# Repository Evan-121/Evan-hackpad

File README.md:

# Evan-hackpad

i used an oled screen, 9 keys/switches, and a xiao prosessor 

all the switches anre linked into the xiao and so is the oled so when i plug it in i can program the buttons to run spesific functions

i will use it to game controll music and  use it to controll some of my other arduino/razberry pi progects

i then designed the case in fusion and brought in the pcb to test the fit

i then got the modells from grabcad and assembled it all in fusion

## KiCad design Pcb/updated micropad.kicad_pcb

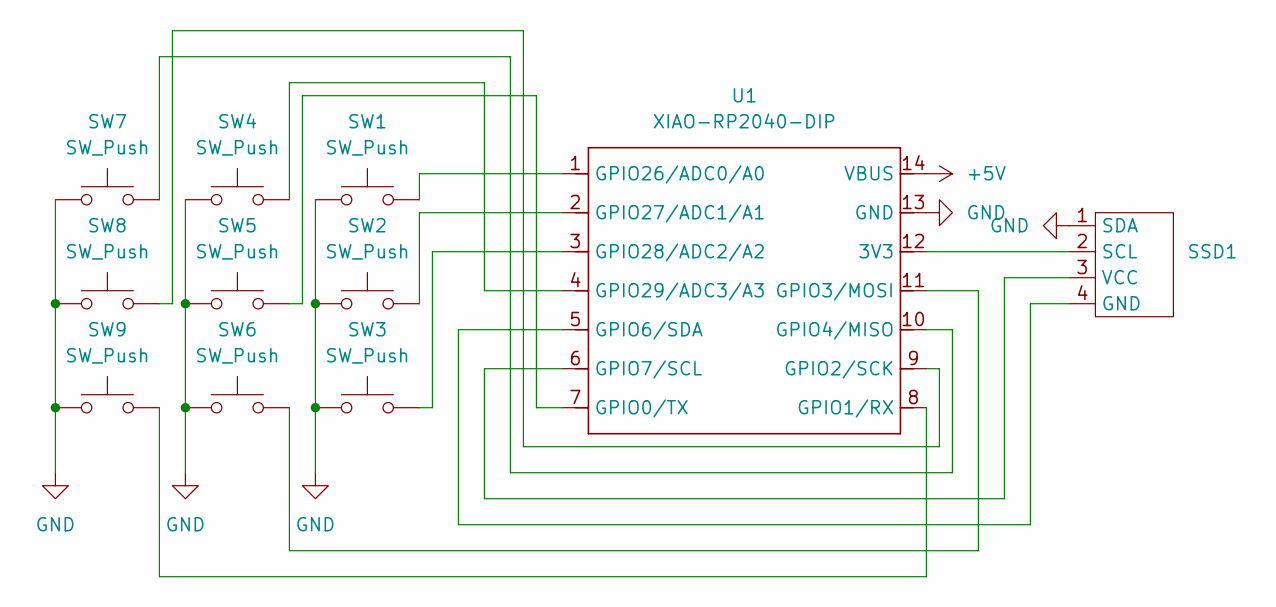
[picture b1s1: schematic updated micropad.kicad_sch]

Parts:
SSD1: SSD1306-0.91-OLED-4pin-128x32 (4)
SW1, SW2, SW3, SW4, SW5, SW6, SW7, SW8, SW9: SW_Push; SW_Cherry_MX_1.00u_PCB
U1: XIAO-RP2040-DIP

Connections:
+5V: U1.14 (VBUS)
GND: SSD1.1 (SDA), SW1.1, SW2.1, SW3.1, SW4.1, SW5.1, SW6.1, SW7.1, SW8.1, SW9.1, U1.13 (GND)
unnamed: SSD1.4 (GND), U1.5 (GPIO6/SDA)
unnamed: SSD1.2 (SCL), U1.12 (3V3)
unnamed: SSD1.3 (VCC), U1.6 (GPIO7/SCL)
unnamed: SW5.2, U1.7 (GPIO0/TX)
unnamed: SW9.2, U1.8 (GPIO1/RX)
unnamed: SW8.2, U1.9 (GPIO2/SCK)
unnamed: SW6.2, U1.11 (GPIO3/MOSI)
unnamed: SW7.2, U1.10 (GPIO4/MISO)
unnamed: SW1.2, U1.1 (GPIO26/ADC0/A0)
unnamed: SW2.2, U1.2 (GPIO27/ADC1/A1)
unnamed: SW3.2, U1.3 (GPIO28/ADC2/A2)
unnamed: SW4.2, U1.4 (GPIO29/ADC3/A3)

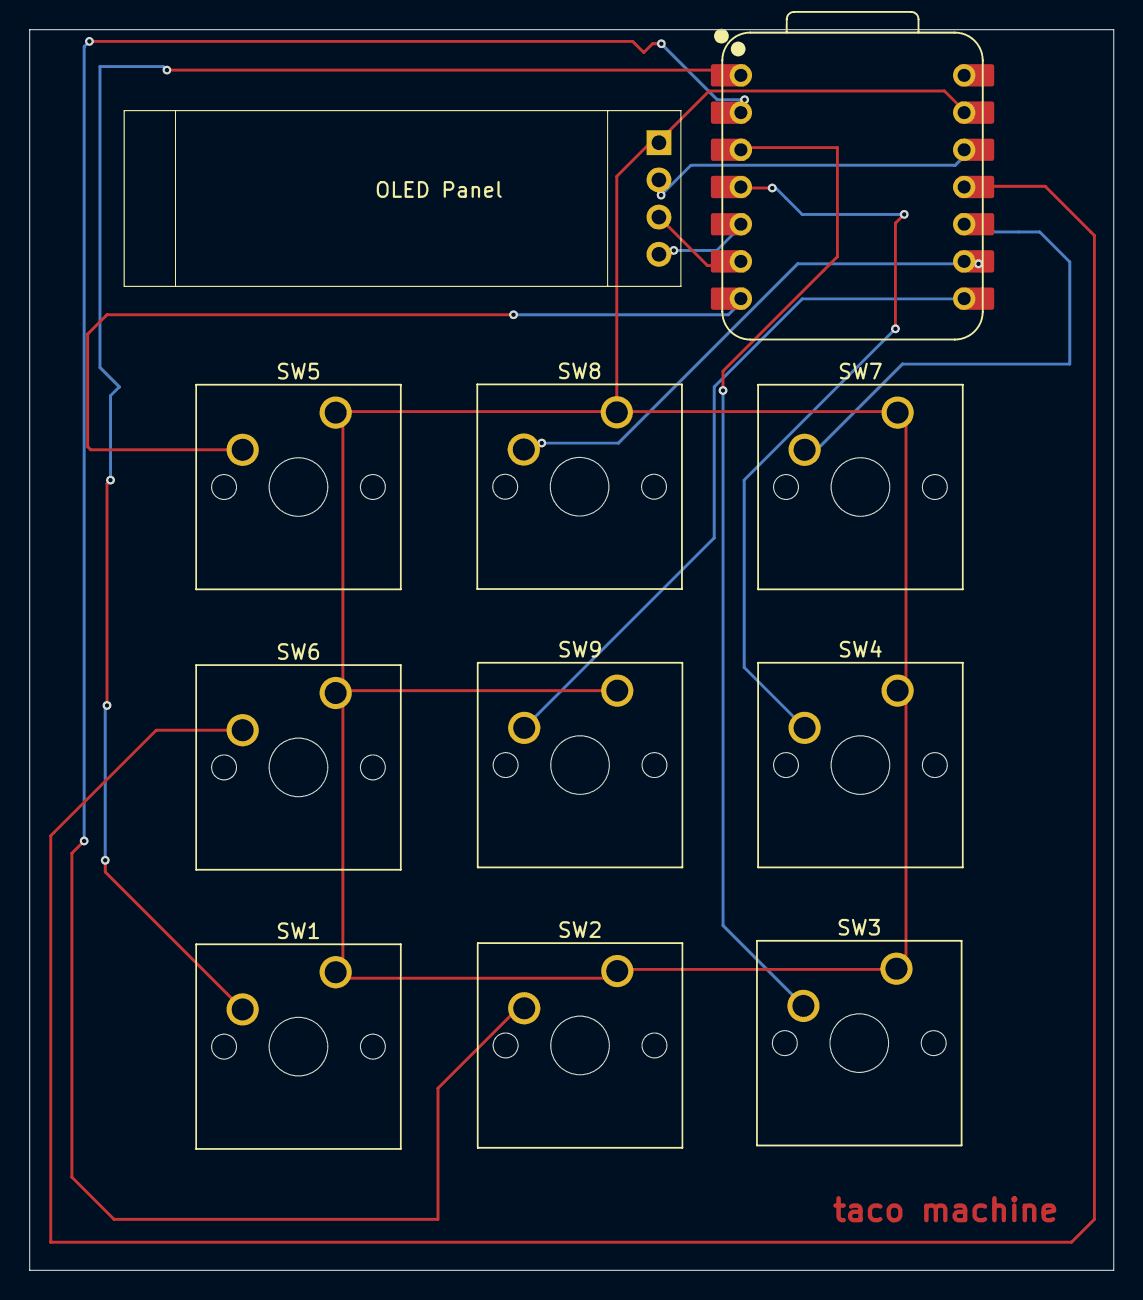
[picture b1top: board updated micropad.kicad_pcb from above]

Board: 2 copper layers, 74.0 x 84.7 mm, 11 parts (0 on the bottom side), 13 nets.

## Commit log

2025-12-15 Revise README for clarity and fix typos
    Correct spelling errors and improve clarity in README.
2025-12-16 Enhance README with project information and images
    Updated README to include additional project details and images.
2025-12-16 Enhance README with project information and images
    Updated README with additional project details and images.
2025-12-16 Clean up README by removing PCB configuration details
    Removed extensive details about PCB settings and configurations.
2025-12-16 Remove README.md file
2025-12-21 Update README with corrections and additional details
    Corrected typos and improved clarity in the README.
2025-12-21 Add files via upload
    this is the file for my pcb
2025-12-21 Add files via upload
    fusion base
2025-12-21 Update README with project details and images
    Added additional details about the project and images.
2026-01-10 Add PCB fit test image to README
    Added an image of the PCB fit test in the README.
2026-01-10 Add image for PCB fit testing in README
    Added an image to demonstrate the PCB fit testing.
2026-01-10 Add files via upload
    this is the lid for the hackpad
2026-01-10 Add files via upload
    this is the base where all the components will sit
2026-01-10 Fix typos in README.md
2026-01-10 Add files via upload
    i used models from grabcad to tes fit it
2026-01-10 Add files via upload
    this is the base where all my components will sit
2026-01-10 Add files via upload
    basic code for the hackpad
2026-01-15 Rename updated micropad.kicad_prl to Pcb/updated micropad.kicad_prl
2026-01-15 Rename updated micropad.kicad_pro to pcb/updated micropad.kicad_pro
2026-01-15 Rename updated micropad.kicad_pro to updated micropad.kicad_pro
2026-01-15 Rename micropad (~recovered).step to 3d models/micropad (~recovered).step
2026-01-15 Rename lid for hackpad.3mf to 3d models/lid for hackpad.3mf
2026-01-15 Rename micropad.3mf to 3d models/micropad.3mf
2026-01-15 Rename main.py to Code/main.py
2026-01-19 Rename micropad (~recovered).step to 3d models/new micropad (~recovered).step
